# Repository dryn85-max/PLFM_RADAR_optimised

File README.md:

# AERIS-10 Lite

AERIS-10 Lite is a reduced, low-cost prototype of the open-source AERIS-10
pulse-LFM phased-array radar: **4 receive/transmit channels instead of 16**, a
single development-board LO, and a vendor-neutral FPGA design that targets a
Cyclone development board. It is a fork of
[NawfalMotii79/PLFM_RADAR](https://github.com/NawfalMotii79/PLFM_RADAR)
("AERIS-10"); see [Upstream and attribution](#upstream-and-attribution).

> **Status: simulation and host tests only. Nothing has been tested on
> hardware.** The FPGA regression, the firmware host tests, the host GUI tests
> and the cross-layer contract tests pass; no board has been powered up. The PLL
> register tables in the firmware are **placeholders**, so the LO will not lock
> until real register exports are added (see [BACKLOG.md](BACKLOG.md) and
> [docs/bring-up.md](docs/bring-up.md)).

## What the prototype is

| Block | Part / choice |
|---|---|
| Beamformer | 1x ADAR1000 (4 channels) |
| Front ends | 4x ADTR1107 (LNA + PA + T/R switch) |
| LO | single PLL evaluation board: ADF4372 or LMX2594 (selected at build time, placeholder tables) |
| FPGA | Intel/Altera Cyclone development board, **board TBD**; the RTL is vendor-neutral Verilog-2001 (no vendor primitives, inferred DSP and RAM) |
| ADC | 12-bit CMOS, 100 MSPS, 20 MHz IF |
| DAC | 8-bit, chirp generation (120 MHz DAC clock) |
| Host link | FT232H / FT2232H in 245 synchronous FIFO mode (USB 2.0) |
| MCU | ST NUCLEO-G0B1RE (STM32G0B1RET6, Cortex-M0+, 64 MHz) |
| Host software | PyQt6 V7 GUI (upstream, unchanged; not yet adapted to 4 channels) |

## Block diagram

```
                       +---------------------------+
   host PC  <--USB2--> | FT232H / FT2232H (245 FIFO)|
 (PyQt6 GUI)           +-------------+-------------+
                                     | 8-bit bus
                         +-----------v-----------+      DIG0..DIG4 (MCU -> FPGA)
   ADC 12 bit  -------->  |   Cyclone dev board   | <------------------------+
   100 MSPS / 20 MHz IF   |  vendor-neutral RTL   |      DIG5..DIG7 (FPGA -> MCU)
   DAC 8 bit   <--------  |  DDC, matched filter, | -----------------------+ |
   (chirp)                |  Doppler, CFAR, USB   |                        | |
                          +-----------------------+                        | |
                                                                  +--------v-v--------+
   LO PLL eval board  <-- SPI1 (8 MHz) --------------------------+  NUCLEO-G0B1RE     |
   (ADF4372 / LMX2594)                                            |  firmware: power   |
   ADAR1000 (4 ch)    <-- SPI2 (16 MHz) --------------------------+  sequencing, beam, |
   ADTR1107 x4 (T/R)  <-- ADAR1000 TR / bias outputs              |  AGC outer loop,   |
   ADS7830 temperature <-- I2C1 (100 kHz)                         |  faults, UART      |
                                                                  +----------+---------+
                                          USART2 via ST-LINK VCP (115200 8N1) |
                                                                    text commands / STATUS
```

More detail (interfaces, DIG0-7 table, clocks, budgets):
[docs/architecture.md](docs/architecture.md).

## Quick start

All commands run from the repository root unless stated. Package installs
**must** use the `sfw` prefix (see [CONTRIBUTING.md](CONTRIBUTING.md)).

### FPGA (`fpga/`)

Needs `iverilog`; the golden-vector generators need Python with numpy.

```
(cd fpga && bash run_regression.sh)    # lint, vendor-neutrality and resource gates, 38 testbenches
git checkout -- fpga/tb/cosim          # the script rewrites tracked CSVs; restore them
```

Module guide, signal chain, rates/widths, resource budget and hand-off list:
[fpga/README.md](fpga/README.md).

### Firmware (`stm32/`)

Needs `arm-none-eabi-gcc` (13.2.1 used), `gcc`, `make`; `st-flash` or
`STM32_Programmer_CLI` for flashing.

```
cd stm32
make test                              # host unit tests (ADAR_COUNT=1 and 4)
make                                   # build ELF/BIN/HEX and run the size check
make DIAG=0 clean all                  # build without diagnostic logging
make ADAR_COUNT=4 clean all            # build for four ADAR1000 devices
make flash                             # ST-LINK (make flash PROGRAMMER=cube for STM32_Programmer_CLI)
```

Pin map, serial command interface, fault model and memory report:
[stm32/README.md](stm32/README.md).

### ESP32 MVP (`esp32/`)

A bench MVP from an ESP32-S3-DevKitC-1 and an HLK-LD2410C 24 GHz presence
radar, with an optional GPS (GY-NEO6MV2) and IMU (GY-BMI160) for UTC time,
position and tilt; it needs no STM32 and no FPGA. Host tests need only `gcc` and `make`;
building the firmware needs ESP-IDF v5.5.5 (CI builds it in a container).

```
make -C esp32/tests test                                              # host tests
(cd esp32 && idf.py set-target esp32s3 && idf.py build flash monitor)  # native USB port
# join the Wi-Fi AERIS-MVP-XXXX (password is printed on the console), open http://192.168.4.1
uv run python host/ld2410_rec.py record aeris-mvp.local -o run.ldrec
uv run python host/ld2410_rec.py export-csv run.ldrec -o run.csv
```

Wiring (read the power warning first), protocol layouts and the VERIFY list:
[esp32/README.md](esp32/README.md).

### Host (`host/`)

```
sfw uv pip install -r host/requirements_v7.txt
python host/GUI_V7_PyQt.py             # GUI
python host/smoke_test.py              # board bring-up script, mock mode (--live for real FT2232H)
QT_QPA_PLATFORM=offscreen uv run pytest host/test_v7.py host/test_radar_protocol.py -v
```

See [host/README.md](host/README.md).

### Cross-layer contract tests (`tests/cross_layer/`)

```
uv run pytest tests/cross_layer/test_cross_layer_contract.py -v
```

These check that the FPGA RTL, the G0B1 firmware and the host GUI agree on
opcodes, the USB packet format and the DIG0-7 GPIO contract.

### Lint

```
uv run ruff check .
```

## Repository map

| Path | Contents |
|---|---|
| `fpga/` | Vendor-neutral Verilog RTL, testbenches, golden vectors, regression script ([README](fpga/README.md)) |
| `stm32/` | STM32G0B1 (NUCLEO-G0B1RE) bare-metal C firmware, host unit tests ([README](stm32/README.md)) |
| `esp32/` | ESP32-S3 + HLK-LD2410C MVP (optional GPS and IMU): live web page and recording server, ESP-IDF C, host tests ([README](esp32/README.md)) |
| `host/` | V7 PyQt6 GUI, USB protocol layer, smoke test, ESP32 recorder `ld2410_rec.py` ([README](host/README.md)) |
| `tests/cross_layer/` | Cross-layer contract tests (RTL / firmware / host) |
| `tools/` | Helper scripts (`uart_capture.py`) and the path gate (`check_paths.sh`) |
| `hardware/datasheets/` | Datasheets of the parts the project uses (ADAR1000, ADTR1107, ADS7830, TMP35/36/37, FT2232H) |
| `docs/` | [architecture](docs/architecture.md), [bring-up](docs/bring-up.md), [decisions](docs/decisions.md), [BOM analysis](docs/bom-optimization.md) (historical, Russian), `superpowers/` (specs and plans) |
| `legacy/` | Upstream material Lite does not use, under its original relative paths ([README](legacy/README.md)) |
| `BACKLOG.md` | Follow-up work and open verification items |
| `AGENTS.md`, `CLAUDE.md` | Guidance for AI coding agents |
| `Licence` | CERN-OHL-P v2 text |

## Documentation

- [docs/architecture.md](docs/architecture.md) - system design, interfaces, clocks, budgets
- [docs/bring-up.md](docs/bring-up.md) - hardware requirements and ordered bring-up checklist
- [docs/decisions.md](docs/decisions.md) - dated log of owner decisions
- [docs/bom-optimization.md](docs/bom-optimization.md) - historical analysis of the upstream design (Russian)
- [docs/superpowers/](docs/superpowers/) - specs and plans of the work done so far
- [BACKLOG.md](BACKLOG.md) - open items
- Module READMEs: [fpga](fpga/README.md), [firmware](stm32/README.md), [esp32](esp32/README.md), [host](host/README.md), [legacy](legacy/README.md)

## Upstream and attribution

AERIS-10 Lite is a fork of
[NawfalMotii79/PLFM_RADAR](https://github.com/NawfalMotii79/PLFM_RADAR)
("AERIS-10: Open Source Pulse Linear Frequency Modulated Phased Array Radar").
The fork baseline is upstream commit `b46dd71`. Upstream material that Lite does
not use (the 16-channel hardware design, Xilinx flows, older GUIs, the HTML
site) is kept in [`legacy/`](legacy/README.md) with its history. Thanks to the
upstream author and contributors.

## Licences

The project uses different licences for hardware and software, as upstream does:

- **Hardware** designs and documentation: CERN Open Hardware Licence Version 2 -
  Permissive (CERN-OHL-P v2). The full text is in the [`Licence`](Licence) file.
- **Software** (firmware, FPGA RTL, host code, scripts): MIT, where not
  otherwise specified.

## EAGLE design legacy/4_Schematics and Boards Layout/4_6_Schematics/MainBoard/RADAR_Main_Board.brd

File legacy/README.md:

# legacy/

Back to the [root README](../README.md).

Reference material inherited from the upstream project
[NawfalMotii79/PLFM_RADAR](https://github.com/NawfalMotii79/PLFM_RADAR)
(baseline upstream commit `b46dd71`) that AERIS-10 Lite does not use.

Everything here was moved with `git mv`, so history is preserved, and keeps its
original relative path (`X` became `legacy/X`), with one exception: the upstream
GitHub Pages site `docs/` became `legacy/docs-site/`. `legacy/` is reference only and
is not built. The one exception: the STM32F7 firmware unit tests in
`9_Firmware/9_1_Microcontroller/tests/` are kept in CI (job "Legacy F7 MCU tests")
as required by the G0B1 spec; run them with
`make -C legacy/9_Firmware/9_1_Microcontroller/tests clean all`.

## Moved items

| Item | Why it is not used by AERIS-10 Lite |
|---|---|
| `1_Project_Description/` | Upstream project description (docx); describes the XC7A100T/upstream design, not Lite. |
| `2_Functional Diagram & Interconnection Matrices/` | Upstream RADAR_V6 block diagram and interconnection matrices for the original 10.5 GHz / multi-board hardware. |
| `3_Power Management/` | Upstream power-board spreadsheet and schematic; Lite has its own power tree. |
| `4_Schematics and Boards Layout/` | Upstream schematics, Gerbers, BOM/CPL for the original boards; Lite hardware is a different design. |
| `5_Simulations/` | Upstream antenna, filter and radar simulations for the original RF chain. |
| `6_Application Notes/` | Upstream application note (UG-290) for the original hardware. |
| `7_Components Datasheets and Application notes/` | Datasheets of parts Lite does not use. The five we do use (ADAR1000, ADTR1107, ADS7830, TMP35/36/37, FT2232H) live in `hardware/datasheets/`. |
| `8_Utils/` | Upstream images, Eagle CAD libraries, mechanical drawings and helper scripts for the original hardware. |
| `docs-site/` (originally `docs/`: `*.html`, `*.pdf`, `assets/`, `artifacts/`, `.nojekyll`) | Upstream GitHub Pages site, reports and Xilinx TE0713 bring-up artifacts; they describe the upstream system. Lite's own plans and specs stay in `docs/superpowers/`. |
| `9_Firmware/9_1_Microcontroller/` | Upstream STM32F7 firmware (libraries, algorithms, application code) and its unit tests. Kept as reference for the G0B1 port; the unit tests under `tests/` still run in CI as "Legacy F7 MCU tests" per the G0B1 spec. |
| `9_Firmware/9_2_FPGA/` | Xilinx-only parts of the upstream FPGA tree: build scripts, constraints (XC7A50T/XC7A200T boards) and the TE0712/TE0713 development tops. Lite's FPGA design is in `fpga/`. |
| `9_Firmware/9_3_GUI/` | Older GUIs (V5, V6, V6.5 Tk, PyQt map) with their requirements, `adi_agc_analysis.py` (needs `host/v7/agc_sim.py` on its import path) and `test_radar_data.csv`. `test_GUI_V65_Tk.py` is no longer run in CI and is not importable here (it needs `radar_protocol` and the Tk GUI on its path); its non-Tk protocol tests now live in `host/test_radar_protocol.py`. Lite uses the V7 GUI in `host/`. |
| `9_Firmware/tests/cross_layer/stm32_settings_stub.cpp` | Upstream F7 settings stub for the old cross-layer tests; the active contract tests are in `tests/cross_layer/` and target `firmware/` (G0B1). |

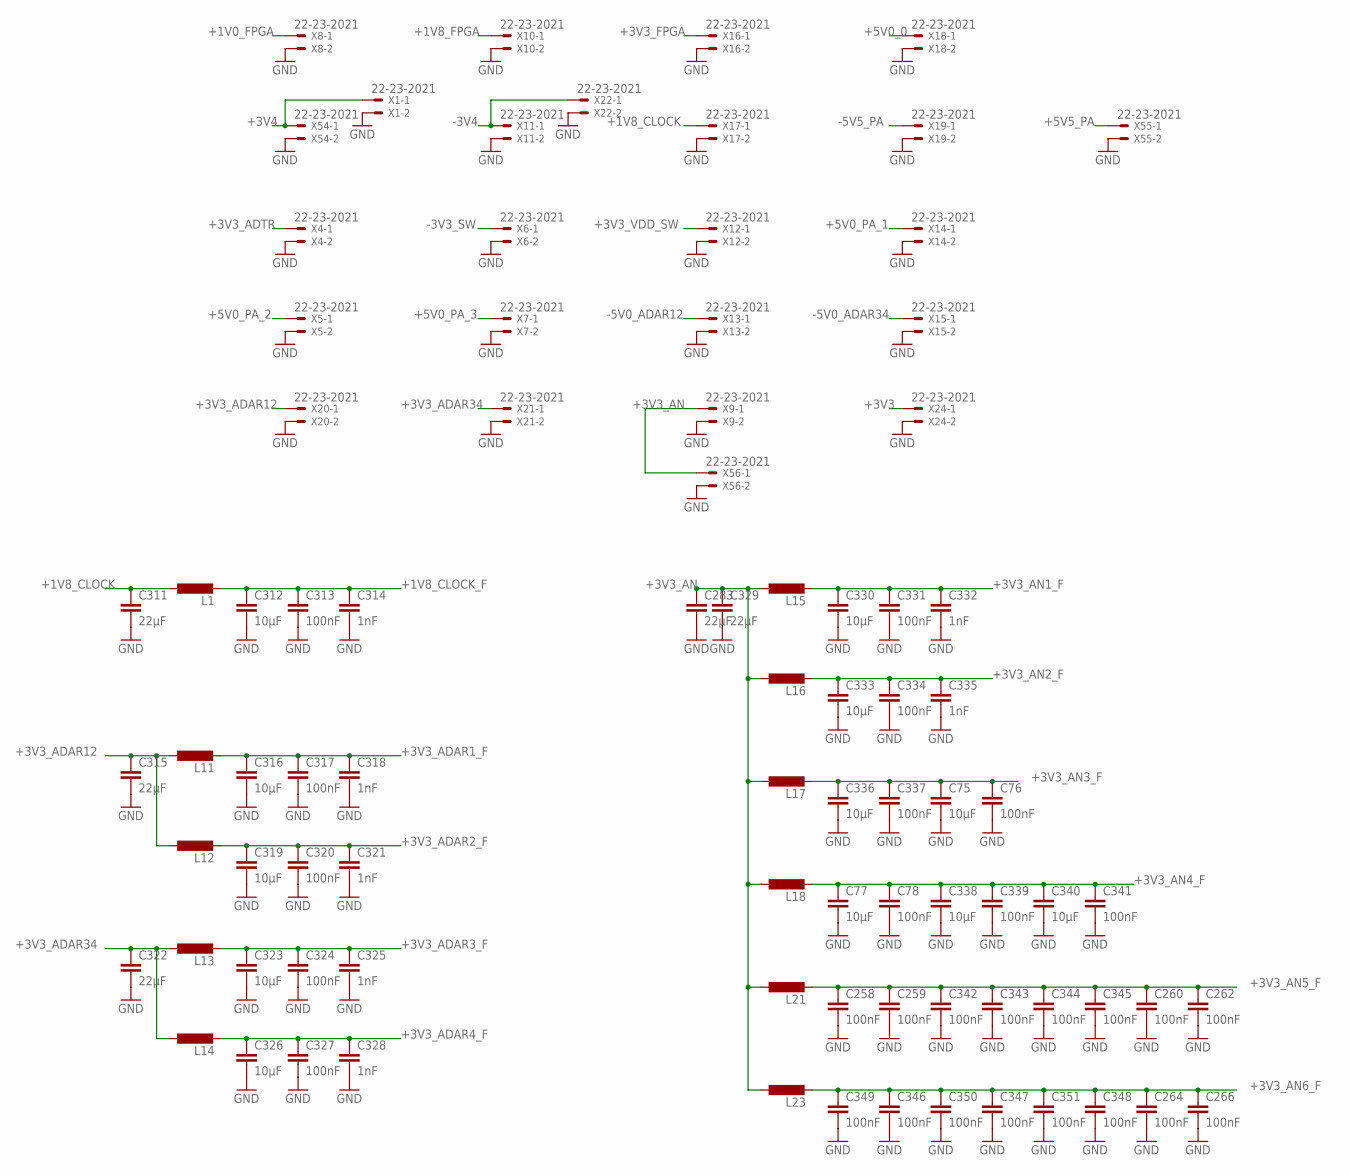
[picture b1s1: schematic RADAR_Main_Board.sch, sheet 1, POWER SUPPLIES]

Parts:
C75, C77, C312, C316, C319, C323, C326, C330, C333, C336, C338, C340: 10µF; C0805
C76, C78, C258, C259, C260, C262, C264, C266, C313, C317, C320, C324, C327, C331, C334, C337, C339, C341, C342, C343, C344, C345, C346, C347, C348, C349, C350, C351: 100nF; C0402
C283, C311, C315, C322, C329: 22µF; C1206
C314, C318, C321, C325, C328, C332, C335: 1nF; C0402
L1, L11, L12, L13, L14, L15, L16, L17, L18, L21, L23: L-EUL5650M; L5650M
X1, X4, X5, X6, X7, X8, X9, X10, X11, X12, X13, X14, X15, X16, X17, X18, X19, X20, X21, X22, X24, X54, X55, X56: 22-23-2021

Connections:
+1V0_FPGA: X8.1; also elsewhere on the board
+1V8_CLOCK: C311.1, L1.1, X17.1
+1V8_CLOCK_F: C312.1, C313.1, C314.1, L1.2; also elsewhere on the board
+1V8_FPGA: X10.1; also elsewhere on the board
+3V3: X24.1; also elsewhere on the board
+3V3_ADAR1_F: C316.1, C317.1, C318.1, L11.2; also elsewhere on the board
+3V3_ADAR2_F: C319.1, C320.1, C321.1, L12.2; also elsewhere on the board
+3V3_ADAR3_F: C323.1, C324.1, C325.1, L13.2; also elsewhere on the board
+3V3_ADAR4_F: C326.1, C327.1, C328.1, L14.2; also elsewhere on the board
+3V3_ADAR12: C315.1, L11.1, L12.1, X20.1
+3V3_ADAR34: C322.1, L13.1, L14.1, X21.1
+3V3_ADTR: X4.1; also elsewhere on the board
+3V3_AN: C283.1, C329.1, L15.1, L16.1, L17.1, L18.1, L21.1, L23.1, X9.1, X56.1; also elsewhere on the board
+3V3_AN1_F: C330.1, C331.1, C332.1, L15.2; also elsewhere on the board
+3V3_AN2_F: C333.1, C334.1, C335.1, L16.2; also elsewhere on the board
+3V3_AN3_F: C75.1, C76.1, C336.1, C337.1, L17.2; also elsewhere on the board
+3V3_AN4_F: C77.1, C78.1, C338.1, C339.1, C340.1, C341.1, L18.2; also elsewhere on the board
+3V3_AN5_F: C258.1, C259.1, C260.1, C262.1, C342.1, C343.1, C344.1, C345.1, L21.2; also elsewhere on the board
+3V3_AN6_F: C264.1, C266.1, C346.1, C347.1, C348.1, C349.1, C350.1, C351.1, L23.2; also elsewhere on the board
+3V3_FPGA: X16.1; also elsewhere on the board
+3V3_VDD_SW: X12.1; also elsewhere on the board
+3V4: X1.1, X54.1; also elsewhere on the board
+5V0_0: X18.1; also elsewhere on the board
+5V0_PA_1: X14.1; also elsewhere on the board
+5V0_PA_2: X5.1; also elsewhere on the board
+5V0_PA_3: X7.1; also elsewhere on the board
+5V5_PA: X55.1; also elsewhere on the board
-3V3_SW: X6.1; also elsewhere on the board
-3V4: X11.1, X22.1; also elsewhere on the board
-5V0_ADAR12: X13.1; also elsewhere on the board
-5V0_ADAR34: X15.1; also elsewhere on the board
-5V5_PA: X19.1; also elsewhere on the board
GND: C75.2, C76.2, C77.2, C78.2, C258.2, C259.2, C260.2, C262.2, C264.2, C266.2, C283.2, C311.2, C312.2, C313.2, C314.2, C315.2, C316.2, C317.2, C318.2, C319.2, C320.2, C321.2, C322.2, C323.2, C324.2, C325.2, C326.2, C327.2, C328.2, C329.2, C330.2, C331.2, C332.2, C333.2, C334.2, C335.2, C336.2, C337.2, C338.2, C339.2, C340.2, C341.2, C342.2, C343.2, C344.2, C345.2, C346.2, C347.2, C348.2, C349.2, C350.2, C351.2, X1.2, X4.2, X5.2, X6.2, X7.2, X8.2, X9.2, X10.2, X11.2, X12.2, X13.2, X14.2, X15.2, X16.2, X17.2, X18.2, X19.2, X20.2, X21.2, X22.2, X24.2, X54.2, X55.2, X56.2; also elsewhere on the board

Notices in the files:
parts and their libraries:
SparkFun-Capacitors: Licensing: Creative Commons ShareAlike 4.0 International - https://creativecommons.org/licenses/by-sa/4.0
COPYRIGHT: Copyright (C) 2024 Ultra Librarian. All rights reserved.
COPYRIGHT: Copyright (C) 2025 Ultra Librarian. All rights reserved.
